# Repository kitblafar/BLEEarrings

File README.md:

# Bluetooth Low-Energy Earrings

A set of bluetooth BLE earrings inspired by the movie blade runner.

Including custom pendant, earring and earring charging dock PCBs; custom 3D printed enclosure; embedded solution on NRF52833 and bluetooth app.

This earring blink different colours dependant on messages sent over Bluetooth by the bluetooth app. The solution includes a pendant that holds the LED and is connected by wiring that passes through the ear piercing; the earring itself that sits behind the ear and a charging and programming dock including USB hub. The earrings are flashed and charged over USB C connectors and are powered by drone batteries so include custom charge protection and power path management circuits.

Project phase: PCB ordered and received, BOM finalised and ordered, first revision of enclosure made, first iteration of the embedded solution.

Next step: test PCBs and NRF52833 code, order batteries, print enclosure, start developing the app.

This is a collab with [Dominic Mason](https://github.com/dominicmason555/)

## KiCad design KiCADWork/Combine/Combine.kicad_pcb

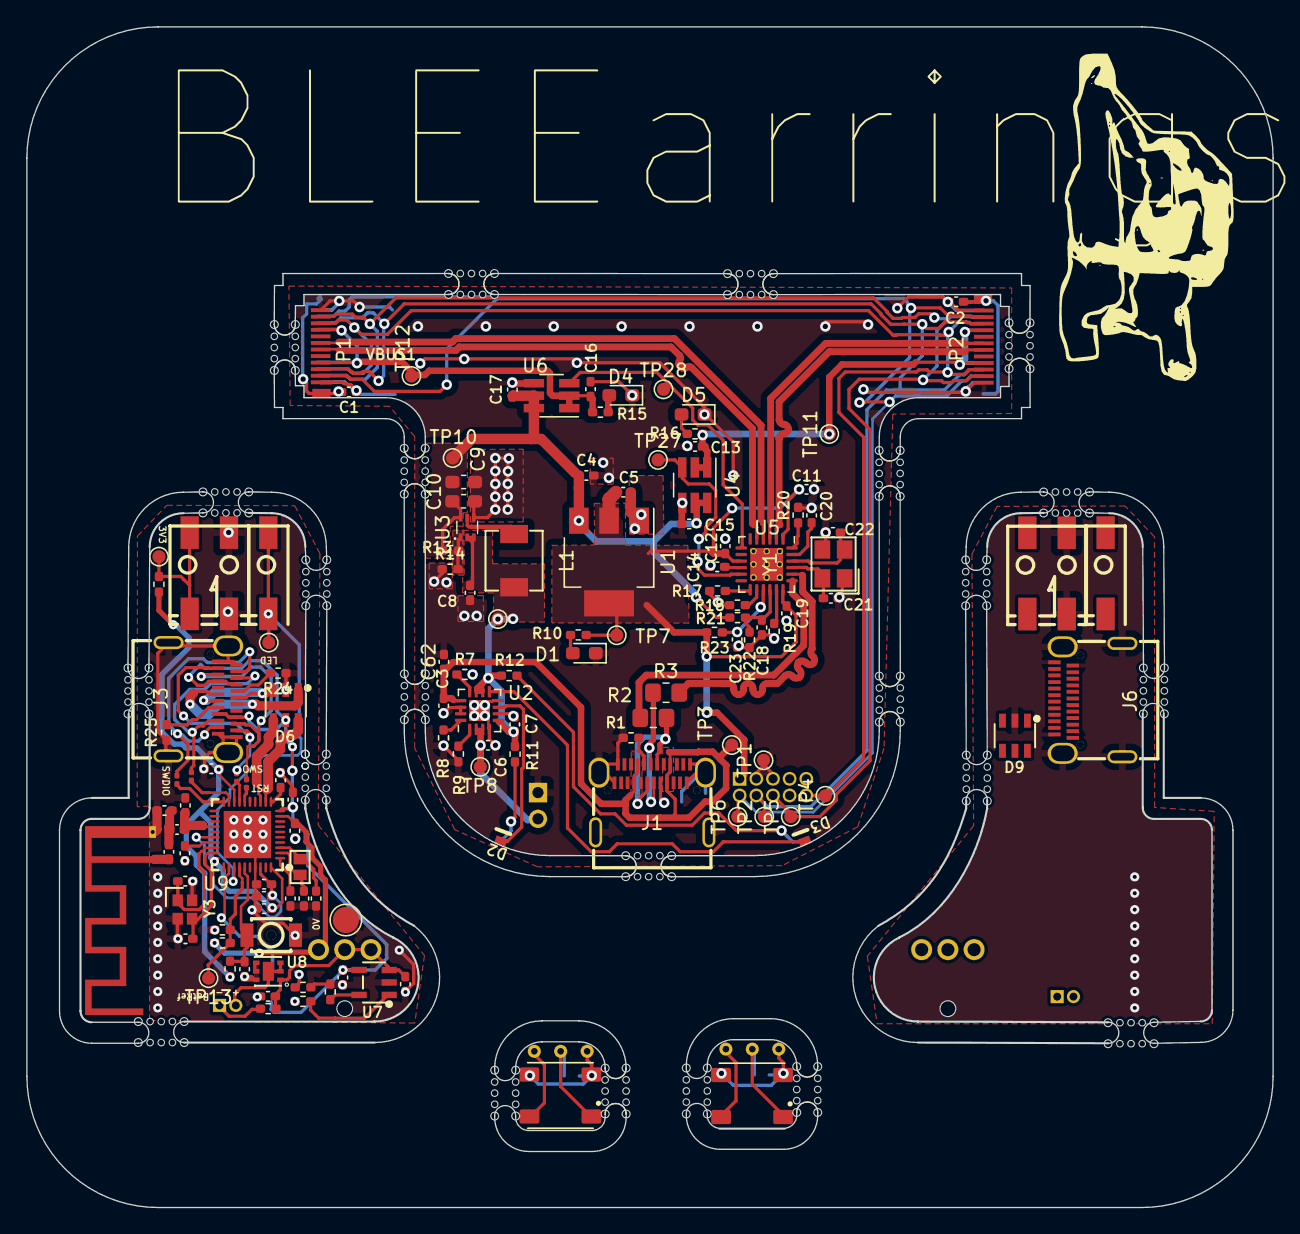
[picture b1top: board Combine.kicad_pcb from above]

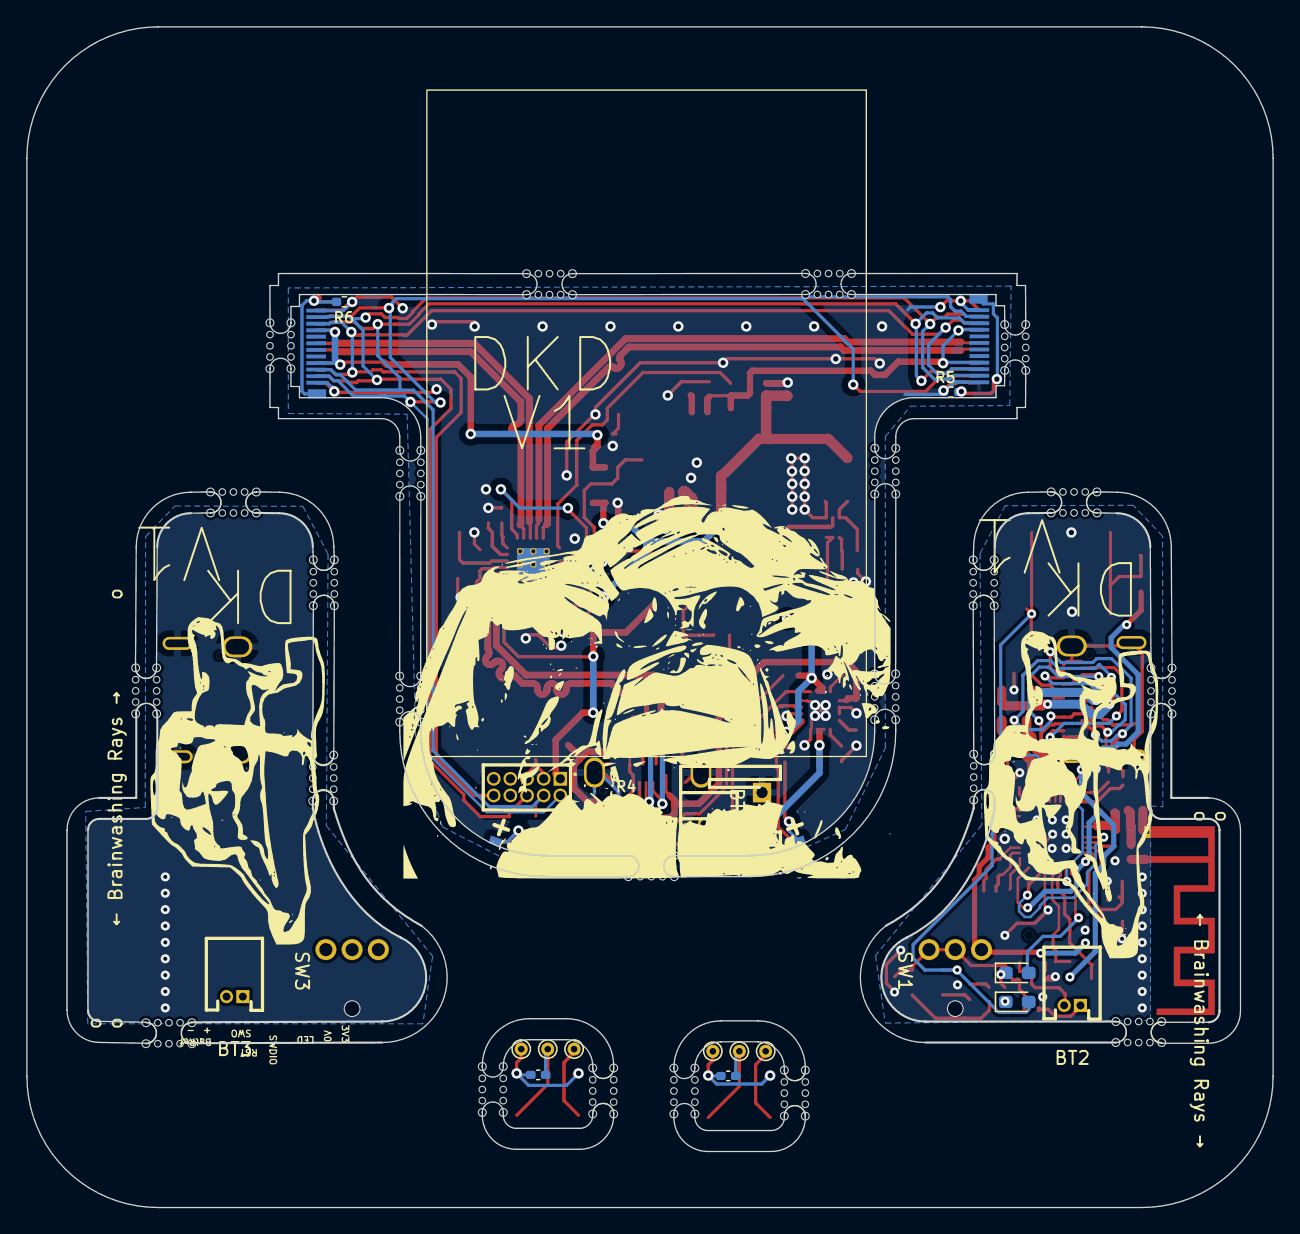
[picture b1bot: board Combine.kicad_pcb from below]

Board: 2 copper layers, 95.0 x 90.0 mm, 149 parts (19 on the bottom side), 98 nets.

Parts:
ANT1: Texas_SWRA117D_2.4GHz_Left
BT1: Battery; CONN-TH_S2B-PH-K-S-LF-SN
BT2, BT3: Battery; CONN-TH_530480210
C1, C2, C11, C13, C16, C18, C19, C20, C25, C30, C33, C41, C63, C64: 100n; C_0402_1005Metric_Pad0.74x0.62mm_HandSolder
C3, C12, C14, C23, C34, C38: 1u; C_0402_1005Metric_Pad0.74x0.62mm_HandSolder
C4, C5: 2.2u; C_0402_1005Metric_Pad0.74x0.62mm_HandSolder
C6, C7, C15, C17, C28, C29, C31: 4.7u; C_0402_1005Metric_Pad0.74x0.62mm_HandSolder
C8, C24, C26, C62: 10u; C_0402_1005Metric_Pad0.74x0.62mm_HandSolder
C9, C10: 22u; C_0603_1608Metric_Pad1.08x0.95mm_HandSolder
C21, C22: 18p; C_0402_1005Metric_Pad0.74x0.62mm_HandSolder
C27, C32: 8p; C_0402_1005Metric_Pad0.74x0.62mm_HandSolder
C35: 1p; C_0402_1005Metric_Pad0.74x0.62mm_HandSolder
C36: 100p; C_0402_1005Metric_Pad0.74x0.62mm_HandSolder
C37: 1.2p; C_0402_1005Metric_Pad0.74x0.62mm_HandSolder
C39: NC; C_0402_1005Metric_Pad0.74x0.62mm_HandSolder
C40, C42: 12p; C_0402_1005Metric_Pad0.74x0.62mm_HandSolder
D1: LED; LED_0603_1608Metric_Pad1.05x0.95mm_HandSolder
D2: BLUE RED; SideStuckLED
D3: BLUE LED; SideStuckLED
D4, D5, D8: BLUE LED; LED_0603_1608Metric_Pad1.05x0.95mm_HandSolder
D6, D9: USBLC6-2SC6_C2687116; SOT-23-6_L2.9-W1.6-P0.95-LS2.8-BL
D7: RED LED; LED_0603_1608Metric_Pad1.05x0.95mm_HandSolder
D12, D13: 2758; SOL320P540X170-4N
J1, J3, J6: USB_C_Receptacle; TYPE-C-SMD_C9900025773
J2: Conn_01x10_Socket; HDR-TH_10P-P1.27-V-M-R2-C5-S1.27-1
J4, J7: Screw_Terminal_01x01; CONN-SMD_custom1
J5, J8: Screw_Terminal_01x02; CONN-SMD_2059-302
L1: 4.7u; IND-SMD_L4.4-W4.2
L2: 4.7n; L_0402_1005Metric_Pad0.77x0.64mm_HandSolder
L3: 2.2n; L_0402_1005Metric_Pad0.77x0.64mm_HandSolder
P1, P2: USB_C_Plug; USB-C-SMD_TYPE-C-24P-GTJB-040
R1, R4, R24, R25: 5k1; R_0402_1005Metric_Pad0.72x0.64mm_HandSolder
R2, R3: 0R; R_0805_2012Metric_Pad1.20x1.40mm_HandSolder
R5, R6: 1k; R_0402_1005Metric_Pad0.72x0.64mm_HandSolder
R7, R11, R12: 1.18k; R_0402_1005Metric_Pad0.72x0.64mm_HandSolder
R8: 1.78k; R_0402_1005Metric_Pad0.72x0.64mm_HandSolder
R9, R21, R22, R23: 10k; R_0402_1005Metric_Pad0.72x0.64mm_HandSolder
R10, R26, R37: 2k; R_0402_1005Metric_Pad0.72x0.64mm_HandSolder
R13: 732; R_0402_1005Metric_Pad0.72x0.64mm_HandSolder
R14, R34: 100k; R_0402_1005Metric_Pad0.72x0.64mm_HandSolder
R15, R16, R29: 220; R_0402_1005Metric_Pad0.72x0.64mm_HandSolder
R17, R18, R19, R28: 100; R_0402_1005Metric_Pad0.72x0.64mm_HandSolder
R20: 12k; R_0402_1005Metric_Pad0.72x0.64mm_HandSolder
R27: 4k99; R_0402_1005Metric_Pad0.72x0.64mm_HandSolder
R30, R31, R32, R33: NF; R_0201_0603Metric
R35: 33k; R_0402_1005Metric_Pad0.72x0.64mm_HandSolder
R36: 470; R_0402_1005Metric_Pad0.72x0.64mm_HandSolder
SW1, SW3: TK-6580B-1; SW-TH_TK-6580B-1
SW2: SW_DIP_x01; KEY-SMD_L3.0-W2.5-LS4.0
TP1, TP2, TP3, TP4, TP5, TP6, TP7, TP8, TP9, TP10, TP11, TP12, TP13, TP14, TP15, TP27, TP28: TestPoint; TestPoint_Pad_D1.0mm
TP16: TestPoint; TestPoint_Pad_D2.0mm
TP21, TP22, TP23, TP24, TP25, TP26: TestPoint; TestPoint_THTPad_D1.0mm_Drill0.5mm
U1: AMS1117-3.3; SOT-223-3_TabPin2
U2: BQ24073RGT; VQFN-16-1EP_3x3mm_P0.5mm_EP1.6x1.6mm
U3: TPS61023DRLR; SOT-563_L1.6-W1.2-P0.50-LS1.6-BR
U4, U6: SIP32509DT-T1-GE3; SOT-23-6_Handsoldering
U5: USB2422T-I/MJ; HVQFN-24-1EP_4x4mm_P0.5mm_EP2.5x2.5mm_ThermalVias
U7: MCP73831T-2ACI/OT; SOT-23-5_L3.0-W1.7-P0.95-LS2.8-BL
U8: XB6096I2SV; WDFN-6_L2.0-W2.0-P0.65-BL-EP
U9: NRF52833-QDAA-R7; QFN-40_L5.0-W5.0-P0.40-TL-EP3.6
Y1: X322524MOB4SI; CRYSTAL-SMD_4P-L3.2-W2.5-BL
Y2: X161032768KLD2SI; CRYSTAL-SMD_L1.6-W1.0
Y3: XL7EL89CKI-111YLC-32M; CRYSTAL-SMD_4P-L2.0-W1.6-BL

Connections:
+3V3: C5.1, C11.2, C12.2, C19.2, C30.1, C34.2, J2.1, R10.2, R23.2, R36.2, R37.2, TP7.1, U1.2 (VO), U5.1 (VDD33), U5.9 (VDD33), U5.18 (VDD33), U9.18 (VDD), U9.30 (VDD), U9.40 (VDD)
+BATT: C28.2, R34.2, SW1.3, SW3.3, U9.9 (VDDH)
/Dock/DeviceSelect/D1+: P2.A6 (D+), U5.3 (USBDP_DN1/PRT_DIS_P1)
/Dock/DeviceSelect/D1-: P2.A7 (D-), U5.2 (USBDM_DN1/PRT_DIS_M1)
/Dock/DeviceSelect/D2+: P1.A6 (D+), U5.5 (USBDP_DN2/PRT_DIS_P2)
/Dock/DeviceSelect/D2-: P1.A7 (D-), U5.4 (USBDM_DN2/PRT_DIS_M2)
/Dock/DeviceSelect/D+: R3.1, U5.20 (USBDP_UP)
/Dock/DeviceSelect/D-: R2.2, U5.19 (USBDM_UP)
/Dock/DeviceSelect/VBUS1: C13.2, P2.A4 (VBUS), P2.A9 (VBUS), P2.B4 (VBUS), P2.B9 (VBUS), R16.1, TP11.1, U4.1 (OUT), U4.2 (OUT)
/Dock/DeviceSelect/VBUS2: C16.2, P1.A4 (VBUS), P1.A9 (VBUS), P1.B4 (VBUS), P1.B9 (VBUS), R15.1, TP12.1, U6.1 (OUT), U6.2 (OUT)
/Dock/DeviceSelect/Vsys: C4.1, C9.1, C10.1, C15.2, C17.2, R13.2, R21.2, TP10.1, U1.3 (VI), U3.6 (VOUT), U4.5 (IN), U4.6 (IN), U6.5 (IN), U6.6 (IN)
/Dock/ExtraBattery/3.7Out: C7.1, C8.1, L1.1, R11.2, R12.2, TP9.1, U2.5 (EN2), U2.10 (OUT), U2.11 (OUT), U3.2 (EN), U3.3 (VIN)
/Dock/ExtraBattery/FB: R13.1, R14.2, U3.1 (FB)
/Dock/ExtraBattery/VBAT: BT1.1 (+), C6.1, TP8.1, U2.2 (BAT), U2.3 (BAT)
/Dock/ExtraBattery/VBUS: C3.1, C62.1, J1.A4 (VBUS), TP3.1, U2.13 (IN)
/Earring1/DSP/VBUS: C26.1, C29.2, D6.5 (VBUS), D7.2 (A), J3.A4 (VBUS), U7.4 (VDD), U9.10 (VBUS)
/Earring1/DSP/nReset: J3.A10 (RX2-), J3.B10 (RX1-), R32.1
/Earring1/Power/VBAT: C24.1, C25.1, R28.2, SW1.1, SW1.2, U7.3 (VBAT), U8.1 (VDD)
/Earring2/DSP/VBUS: D9.5 (VBUS), J6.A4 (VBUS)
/Earring2/DSP/nReset: J6.A10 (RX2-), J6.B10 (RX1-)
/Earring2/Power/VBAT: SW3.1, SW3.2
BatRef: R34.1, R35.2, TP13.1, U9.34 (P0.29_AIN5)
D+: D6.4 (I/O2), D9.4 (I/O2), U9.13 (D+)
D-: D6.6 (I/O1), D9.6 (I/O1), U9.12 (D-)
DEC6: C38.1, C39.1, U9.26 (DEC6), U9.38 (DEC4)
GND: ANT1.2 (GND), BT1.2 (-), C1.1, C2.1, C3.2, C4.2, C5.2, C6.2, C7.2, C8.2, C9.2, C10.2, C11.1, C12.1, C13.1, C14.1, C15.1, C16.1, C17.1, C18.1, C19.1, C20.1, C21.2, C22.1, C23.1, C24.2, C25.2, C26.2, C27.1, C28.1, C29.1, C30.2, C31.1, C32.1, C33.1, C34.1, C35.2, C36.2, C37.2, C38.2, C39.2, C40.1, C41.1, C42.1, C62.2, D1.1 (K), D4.1 (K), D5.1 (K), D6.2 (GND), D9.2 (GND), J1.A1 (GND), J1.S1 (SHIELD), J2.3, J2.5, J3.A1 (GND), J3.S1 (SHIELD), J5.2, J6.A1 (GND), J6.S1 (SHIELD), J8.2, P1.A1 (GND), P2.A1 (GND), R1.1, R4.1, R5.2, R6.2, R7.2, R8.2, R9.1, R14.1, R17.1, R18.1, R19.1, R20.1, R22.1, R24.1, R25.1, R27.2, R29.1, R35.1, SW2.2, TP1.1, TP16.1, U1.1 (GND), U2.4 (~CE), U2.6 (EN1), U2.8 (VSS), U2.14 (TMR), U2.15 (TD), U2.17 (VSS), U3.4 (GND), U4.4 (GND), U5.25 (EP), U6.4 (GND), U7.2 (VSS), U8.4 (VM), U8.5 (VM), U8.6 (VM), U9.37 (VSS), U9.41 (VSS), Y1.1, Y1.3, Y3.2, Y3.3
LED_A: D8.2 (A), U9.32 (P0.02_AIN0)
NEO_LED: J4.1, J7.1, TP14.1, U9.33 (P0.28_AIN4)
unnamed: ANT1.1 (FP), L3.2
unnamed: BT2.1 (+), R28.1
unnamed: BT2.2 (-), U8.2 (GND), U8.3 (GND), U8.7 (EP)
unnamed: C37.1, L2.2, L3.1
unnamed: D1.2 (A), R10.1
unnamed: D2.2 (A), R11.1
unnamed: D2.1 (K), U2.7 (~PGOOD)
unnamed: D3.2 (A), R12.1
unnamed: D3.1 (K), U2.9 (~CHG)
unnamed: D4.2 (A), R15.2
unnamed: D5.2 (A), R16.2
unnamed: D6.1 (I/O1), J3.A7 (D-), J3.B7 (D-)
unnamed: D6.3 (I/O2), J3.A6 (D+), J3.B6 (D+)
unnamed: D7.1 (K), R26.1
unnamed: D8.1 (K), R29.2
unnamed: D9.1 (I/O1), J6.A7 (D-), J6.B7 (D-)
unnamed: D9.3 (I/O2), J6.A6 (D+), J6.B6 (D+)
unnamed: D12.4 (DIN), TP21.1
unnamed: C63.1, D12.2 (DOUT), D12.3 (VSS), TP23.1
unnamed: C63.2, D12.1 (VDD), TP22.1
unnamed: D13.4 (DIN), TP24.1
unnamed: C64.1, D13.2 (DOUT), D13.3 (VSS), TP26.1
unnamed: C64.2, D13.1 (VDD), TP25.1
unnamed: J1.A5 (CC1), R1.2
unnamed: J1.B5 (CC2), R4.2
unnamed: J1.A6 (D+), J1.B6 (D+), R3.2
unnamed: J1.A7 (D-), J1.B7 (D-), R2.1
unnamed: J3.A5 (CC1), R24.2
unnamed: J3.B5 (CC2), R25.2
unnamed: J5.1, R36.1, TP15.1
unnamed: C1.2, P1.S1 (SHIELD), R5.1
unnamed: C2.2, P2.S1 (SHIELD), R6.1
unnamed: R7.1, U2.12 (ILIM)
unnamed: R8.1, U2.16 (ISET)
unnamed: R9.2, U2.1 (TS)
unnamed: L1.2, U3.5 (SW)
unnamed: C14.2, U5.10 (CRFILT)
unnamed: C20.2, U5.23 (PLLFILT)
unnamed: R20.2, U5.24 (RBIAS)
unnamed: R18.2, U5.14 (SMBCLK/CFG_SEL0)
unnamed: R17.2, U5.13 (SMBDATA/NON_REM1)
unnamed: R19.2, U5.17 (SUSP_IND/LOCAL_PWR/(NON_REM0))
unnamed: C18.2, R21.1, R22.2, U5.16 (VBUS_DET)
unnamed: C22.2, U5.22 (XTALIN/CLKIN), Y1.2
unnamed: C21.1, U5.21 (XTALOUT/(CLKIN_EN)), Y1.4
unnamed: R27.1, U7.5 (PROG)
unnamed: R26.2, U7.1 (STAT)
unnamed: C35.1, L2.1, U9.24 (ANT)
unnamed: C33.2, U9.1 (DEC1)
unnamed: C36.1, U9.27 (DEC3)
unnamed: C31.2, U9.11 (DECUSB)
unnamed: C27.2, U9.2 (P0.00_XL1), Y2.2
unnamed: C32.2, U9.3 (P0.01_XL2), Y2.1
unnamed: R32.2, U9.16 (P0.18_nRESET)
unnamed: R30.1, U9.17 (P0.20)
unnamed: R31.1, U9.20 (SWDCLK)
unnamed: R33.2, U9.19 (SWDIO)
unnamed: C42.2, U9.28 (XC1), Y3.1
unnamed: C40.2, U9.29 (XC2), Y3.4
PWREN1: TP27.1, U4.3 (EN), U5.11 (PRTPWR2)
PWREN2: TP28.1, U5.7 (PRTPWR1/(BC_EN1)), U6.3 (EN)
Pair: C41.2, R37.1, SW2.1, U9.35 (P0.30_AIN6)
RESET: C23.2, R23.1, U5.15 (RESET_N)
SWCLK: J2.4, P1.A3 (TX1-), P1.B3 (TX2-), P2.A3 (TX1-), P2.B3 (TX2-), TP2.1
SWDCLK_L: J3.A3 (TX1-), J3.B3 (TX2-), J6.A3 (TX1-), J6.B3 (TX2-), R33.1
SWDIO: J2.2, P1.A2 (TX1+), P1.B2 (TX2+), P2.A2 (TX1+), P2.B2 (TX2+), TP6.1
SWDIO_L: J3.A2 (TX1+), J3.B2 (TX2+), J6.A2 (TX1+), J6.B2 (TX2+), R31.2
SWO: J2.6, P1.A11 (RX2+), P1.B11 (RX1+), P2.A11 (RX2+), P2.B11 (RX1+), TP5.1
SWO_L: J3.A11 (RX2+), J3.B11 (RX1+), J6.A11 (RX2+), J6.B11 (RX1+), R30.2
nRESET: J2.10, P1.A10 (RX2-), P1.B10 (RX1-), P2.A10 (RX2-), P2.B10 (RX1-), TP4.1

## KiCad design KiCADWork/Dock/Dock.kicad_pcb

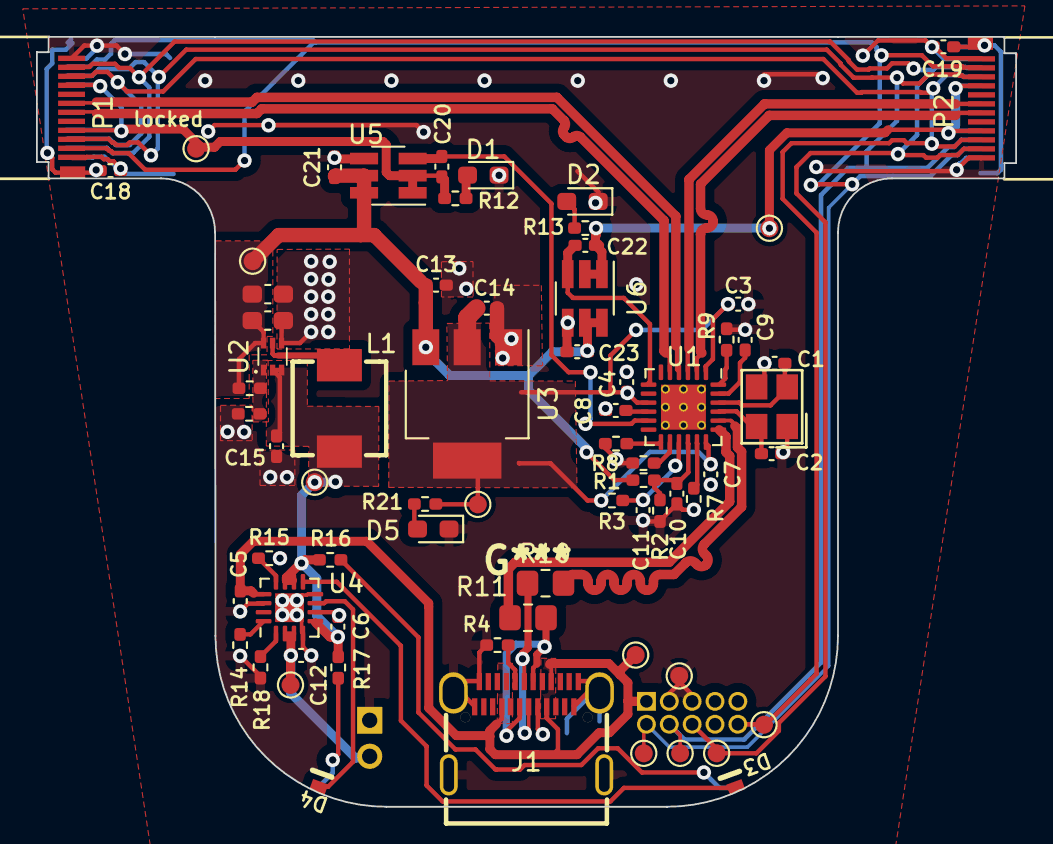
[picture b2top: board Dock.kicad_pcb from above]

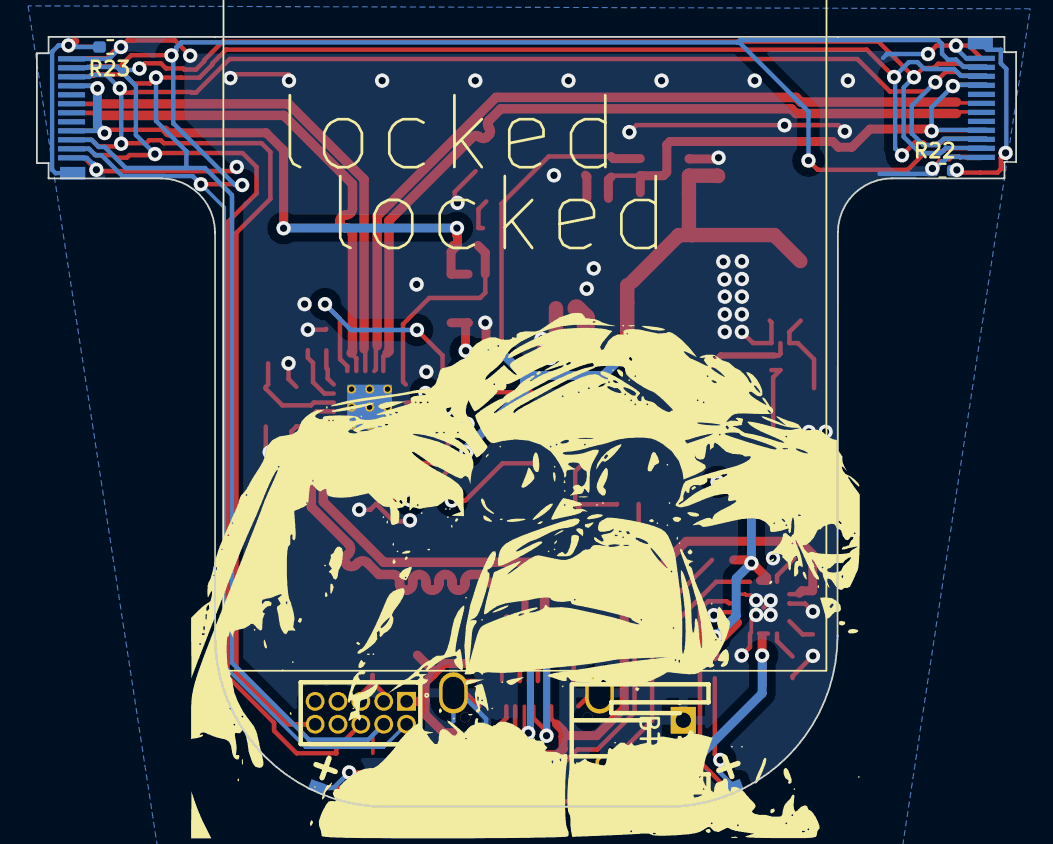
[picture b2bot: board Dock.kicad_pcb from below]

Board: 2 copper layers, 54.4 x 42.8 mm, 76 parts (5 on the bottom side), 48 nets.

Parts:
BT2: Battery; CONN-TH_S2B-PH-K-S-LF-SN
C1, C2: 18p; C_0402_1005Metric_Pad0.74x0.62mm_HandSolder
C3, C7, C9, C10, C18, C19, C20, C22: 100n; C_0402_1005Metric_Pad0.74x0.62mm_HandSolder
C4, C5, C8, C11: 1u; C_0402_1005Metric_Pad0.74x0.62mm_HandSolder
C6, C12, C21, C23: 4.7u; C_0402_1005Metric_Pad0.74x0.62mm_HandSolder
C13, C14: 2.2u; C_0402_1005Metric_Pad0.74x0.62mm_HandSolder
C15: 10u; C_0402_1005Metric_Pad0.74x0.62mm_HandSolder
C16, C17: 22u; C_0603_1608Metric_Pad1.08x0.95mm_HandSolder
D1, D2: BLUE LED; LED_0603_1608Metric_Pad1.05x0.95mm_HandSolder
D3: BLUE LED; SideStuckLED
D4: BLUE RED; SideStuckLED
D5: LED; LED_0603_1608Metric_Pad1.05x0.95mm_HandSolder
J1: USB_C_Receptacle; TYPE-C-SMD_C9900025773
J4: Conn_01x10_Socket; HDR-TH_10P-P1.27-V-M-R2-C5-S1.27-1
L1: 4.7u; IND-SMD_L5.2-W5.2_YSPI0530
P1, P2: USB_C_Plug; USB-C-SMD_TYPE-C-24P-GTJB-040
R1, R2, R3, R18: 10k; R_0402_1005Metric_Pad0.72x0.64mm_HandSolder
R4, R5: 5k1; R_0402_1005Metric_Pad0.72x0.64mm_HandSolder
R6, R7, R8: 100; R_0402_1005Metric_Pad0.72x0.64mm_HandSolder
R9: 12k; R_0402_1005Metric_Pad0.72x0.64mm_HandSolder
R10, R11: 0R; R_0805_2012Metric_Pad1.20x1.40mm_HandSolder
R12, R13: 220; R_0402_1005Metric_Pad0.72x0.64mm_HandSolder
R14: 1.78k; R_0402_1005Metric_Pad0.72x0.64mm_HandSolder
R15, R16, R17: 1.18k; R_0402_1005Metric_Pad0.72x0.64mm_HandSolder
R19: 100k; R_0402_1005Metric_Pad0.72x0.64mm_HandSolder
R20: 732; R_0402_1005Metric_Pad0.72x0.64mm_HandSolder
R21: 2k; R_0402_1005Metric_Pad0.72x0.64mm_HandSolder
R22, R23: 1k; R_0402_1005Metric_Pad0.72x0.64mm_HandSolder
TP3, TP4, TP6, TP7, TP8, TP10, TP11, TP12, TP13, TP14, TP16, TP17: TestPoint; TestPoint_Pad_D1.0mm
U1: USB2422T-I/MJ; HVQFN-24-1EP_4x4mm_P0.5mm_EP2.5x2.5mm_ThermalVias
U2: TPS61023DRLR; SOT-563_L1.6-W1.2-P0.50-LS1.6-BR
U3: AMS1117-3.3; SOT-223-3_TabPin2
U4: BQ24073RGT; VQFN-16-1EP_3x3mm_P0.5mm_EP1.6x1.6mm
U5, U6: SIP32509DT-T1-GE3; SOT-23-6_Handsoldering
Y1: X322524MOB4SI; CRYSTAL-SMD_4P-L3.2-W2.5-BL

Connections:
+3V3: C3.2, C4.2, C7.2, C14.1, R3.2, R21.2, TP10.1, U1.1 (VDD33), U1.9 (VDD33), U1.18 (VDD33), U3.2 (VO)
/DeviceSelect/D1+: P1.A6 (D+), U1.5 (USBDP_DN2/PRT_DIS_P2)
/DeviceSelect/D1-: P1.A7 (D-), U1.4 (USBDM_DN2/PRT_DIS_M2)
/DeviceSelect/D2+: P2.A6 (D+), U1.3 (USBDP_DN1/PRT_DIS_P1)
/DeviceSelect/D2-: P2.A7 (D-), U1.2 (USBDM_DN1/PRT_DIS_M1)
/DeviceSelect/D+: R10.1, U1.20 (USBDP_UP)
/DeviceSelect/D-: R11.2, U1.19 (USBDM_UP)
/DeviceSelect/VBUS1: C20.2, P1.A4 (VBUS), P1.A9 (VBUS), P1.B4 (VBUS), P1.B9 (VBUS), R12.1, TP3.1, U5.1 (OUT), U5.2 (OUT)
/DeviceSelect/VBUS2: C22.2, P2.A4 (VBUS), P2.A9 (VBUS), P2.B4 (VBUS), P2.B9 (VBUS), R13.1, TP4.1, U6.1 (OUT), U6.2 (OUT)
/DeviceSelect/Vsys: C13.1, C16.1, C17.1, C21.2, C23.2, R1.2, R20.2, TP6.1, U2.6 (VOUT), U3.3 (VI), U5.5 (IN), U5.6 (IN), U6.5 (IN), U6.6 (IN)
/ExtraBattery/3.7Out: C6.1, C15.1, L1.1, R16.2, R17.2, TP7.1, U2.2 (EN), U2.3 (VIN), U4.5 (EN2), U4.10 (OUT), U4.11 (OUT)
/ExtraBattery/FB: R19.2, R20.1, U2.1 (FB)
/ExtraBattery/VBAT: BT2.1 (+), C12.1, TP8.1, U4.2 (BAT), U4.3 (BAT)
GND: BT2.2 (-), C1.1, C2.2, C3.1, C4.1, C5.2, C6.2, C7.1, C8.1, C9.1, C10.1, C11.1, C12.2, C13.2, C14.2, C15.2, C16.2, C17.2, C18.1, C19.1, C21.1, C23.1, D1.1 (K), D2.1 (K), D5.1 (K), J1.A1 (GND), J1.S1 (SHIELD), J4.3, J4.5, P1.A1 (GND), P2.A1 (GND), R2.1, R4.1, R5.1, R6.1, R7.1, R8.1, R9.1, R14.2, R15.2, R18.1, R19.1, R22.2, R23.2, TP17.1, U1.25 (EP), U2.4 (GND), U3.1 (GND), U4.4 (~CE), U4.6 (EN1), U4.8 (VSS), U4.14 (TMR), U4.17 (VSS), U5.4 (GND), U6.4 (GND), Y1.1, Y1.3
unnamed: D1.2 (A), R12.2
unnamed: D2.2 (A), R13.2
unnamed: D3.2 (A), R16.1
unnamed: D3.1 (K), U4.9 (~CHG)
unnamed: D4.2 (A), R17.1
unnamed: D4.1 (K), U4.7 (~PGOOD)
unnamed: D5.2 (A), R21.1
unnamed: J1.A5 (CC1), R4.2
unnamed: J1.B5 (CC2), R5.2
unnamed: J1.A6 (D+), J1.B6 (D+), R10.2
unnamed: J1.A7 (D-), J1.B7 (D-), R11.1
unnamed: C18.2, P1.S1 (SHIELD), R22.1
unnamed: C19.2, P2.S1 (SHIELD), R23.1
unnamed: C8.2, U1.10 (CRFILT)
unnamed: C9.2, U1.23 (PLLFILT)
unnamed: R9.2, U1.24 (RBIAS)
unnamed: R8.2, U1.14 (SMBCLK/CFG_SEL0)
unnamed: R6.2, U1.13 (SMBDATA/NON_REM1)
unnamed: R7.2, U1.17 (SUSP_IND/LOCAL_PWR/(NON_REM0))
unnamed: C10.2, R1.1, R2.2, U1.16 (VBUS_DET)
unnamed: C1.2, U1.22 (XTALIN/CLKIN), Y1.2
unnamed: C2.1, U1.21 (XTALOUT/(CLKIN_EN)), Y1.4
unnamed: L1.2, U2.5 (SW)
unnamed: R15.1, U4.12 (ILIM)
unnamed: R14.1, U4.16 (ISET)
unnamed: R18.2, U4.1 (TS)
PWREN1: C20.1, U1.11 (PRTPWR2), U5.3 (EN)
PWREN2: C22.1, U1.7 (PRTPWR1/(BC_EN1)), U6.3 (EN)
RESET: C11.2, R3.1, U1.15 (RESET_N)
SWCLK: J4.4, P1.A3 (TX1-), P1.B3 (TX2-), P2.A3 (TX1-), P2.B3 (TX2-), TP13.1
SWDIO: J4.2, P1.A2 (TX1+), P1.B2 (TX2+), P2.A2 (TX1+), P2.B2 (TX2+), TP12.1
SWO: J4.6, P1.A11 (RX2+), P1.B11 (RX1+), P2.A11 (RX2+), P2.B11 (RX1+), TP14.1
VTRef: C5.1, J1.A4 (VBUS), J4.1, TP11.1, U4.13 (IN)
nRESET: J4.10, P1.A10 (RX2-), P1.B10 (RX1-), P2.A10 (RX2-), P2.B10 (RX1-), TP16.1

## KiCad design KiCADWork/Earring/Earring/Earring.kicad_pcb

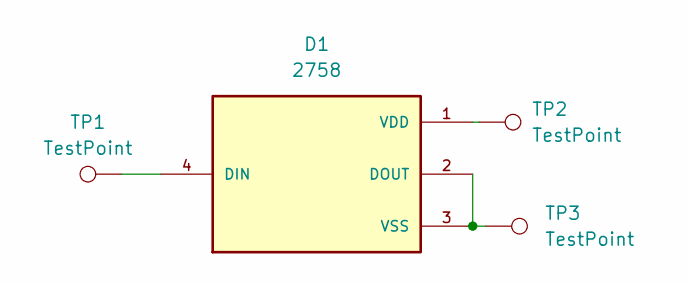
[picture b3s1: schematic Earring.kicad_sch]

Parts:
D1: 2758; SOL320P540X170-4N; PARTREV 01
TP1, TP2, TP3: TestPoint; TestPoint_THTPad_D1.0mm_Drill0.5mm

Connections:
unnamed: D1.4 (DIN), TP1.1
unnamed: D1.2 (DOUT), D1.3 (VSS), TP3.1
unnamed: D1.1 (VDD), TP2.1

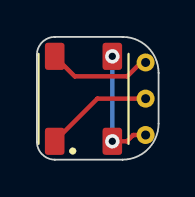
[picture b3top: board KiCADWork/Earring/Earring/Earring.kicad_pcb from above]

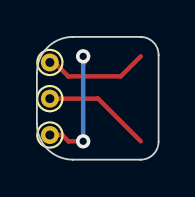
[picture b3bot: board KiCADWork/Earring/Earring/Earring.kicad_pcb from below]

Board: 2 copper layers, 6.8 x 6.8 mm, 4 parts (3 on the bottom side), 3 nets.

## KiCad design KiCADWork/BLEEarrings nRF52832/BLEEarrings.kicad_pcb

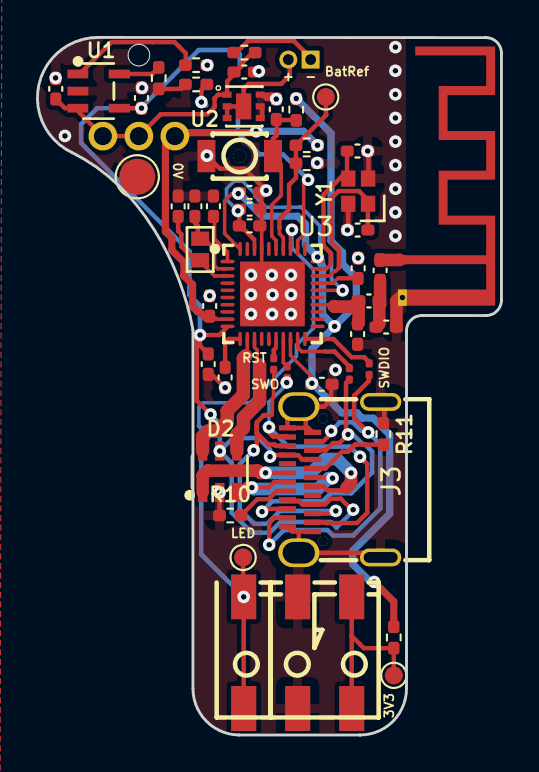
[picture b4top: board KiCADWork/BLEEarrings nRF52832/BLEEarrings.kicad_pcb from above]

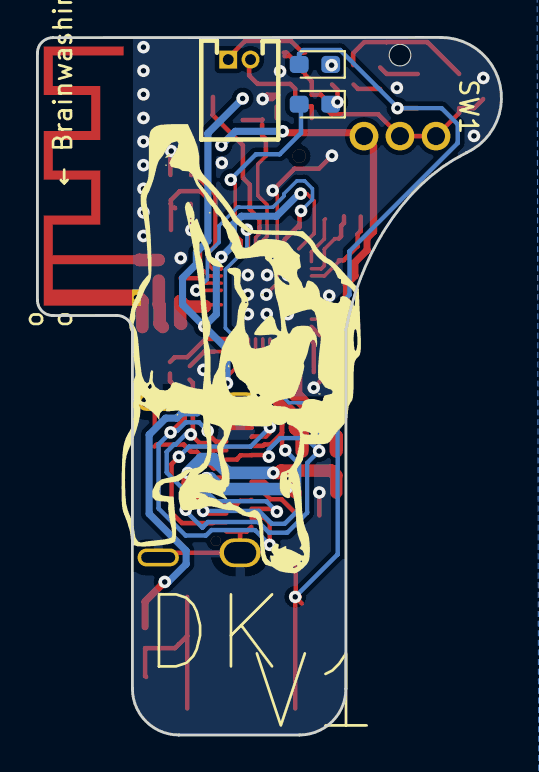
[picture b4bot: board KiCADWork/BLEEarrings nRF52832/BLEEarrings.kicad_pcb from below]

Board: 2 copper layers, 25.8 x 38.8 mm, 54 parts (4 on the bottom side), 41 nets.

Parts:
ANT1: Texas_SWRA117D_2.4GHz_Left
BT1: Battery; CONN-TH_530480210
C1, C7: 1u; C_0402_1005Metric_Pad0.74x0.62mm_HandSolder
C2, C6, C14, C18: 100n; C_0402_1005Metric_Pad0.74x0.62mm_HandSolder
C3, C4: 12p; C_0402_1005Metric_Pad0.74x0.62mm_HandSolder
C5: 1.2p; C_0402_1005Metric_Pad0.74x0.62mm_HandSolder
C8: 1p; C_0402_1005Metric_Pad0.74x0.62mm_HandSolder
C9, C10, C12: 4.7u; C_0402_1005Metric_Pad0.74x0.62mm_HandSolder
C11: 100p; C_0402_1005Metric_Pad0.74x0.62mm_HandSolder
C13, C19: 10u; C_0402_1005Metric_Pad0.74x0.62mm_HandSolder
C15, C16: 8p; C_0402_1005Metric_Pad0.74x0.62mm_HandSolder
C17: NC; C_0402_1005Metric_Pad0.74x0.62mm_HandSolder
D1: RED LED; LED_0603_1608Metric_Pad1.05x0.95mm_HandSolder
D2: USBLC6-2SC6_C2687116; SOT-23-6_L2.9-W1.6-P0.95-LS2.8-BL
D4: BLUE LED; LED_0603_1608Metric_Pad1.05x0.95mm_HandSolder
J1: Screw_Terminal_01x01; CONN-SMD_custom1
J2: Screw_Terminal_01x02; CONN-SMD_2059-302
J3: USB_C_Receptacle; TYPE-C-SMD_C9900025773
L1: 4.7n; L_0402_1005Metric_Pad0.77x0.64mm_HandSolder
L2: 2.2n; L_0402_1005Metric_Pad0.77x0.64mm_HandSolder
R1, R2: 2k; R_0402_1005Metric_Pad0.72x0.64mm_HandSolder
R3: 100; R_0402_1005Metric_Pad0.72x0.64mm_HandSolder
R4: 4k99; R_0402_1005Metric_Pad0.72x0.64mm_HandSolder
R5, R6, R7, R8: NF; R_0201_0603Metric
R9: 470; R_0402_1005Metric_Pad0.72x0.64mm_HandSolder
R10, R11: 5k1; R_0402_1005Metric_Pad0.72x0.64mm_HandSolder
R12: 220; R_0402_1005Metric_Pad0.72x0.64mm_HandSolder
R13: 100k; R_0402_1005Metric_Pad0.72x0.64mm_HandSolder
R14: 33k; R_0402_1005Metric_Pad0.72x0.64mm_HandSolder
SW1: TK-6580B-1; SW-TH_TK-6580B-1
SW2: SW_DIP_x01; KEY-SMD_L3.0-W2.5-LS4.0
TP9, TP10, TP11: TestPoint; TestPoint_Pad_D1.0mm
TP16: TestPoint; TestPoint_Pad_D2.0mm
U1: MCP73831T-2ACI/OT; SOT-23-5_L3.0-W1.7-P0.95-LS2.8-BL
U2: XB6096I2SV; WDFN-6_L2.0-W2.0-P0.65-BL-EP
U3: NRF52833-QDAA-R7; QFN-40_L5.0-W5.0-P0.40-TL-EP3.6
Y1: XL7EL89CKI-111YLC-32M; CRYSTAL-SMD_4P-L2.0-W1.6-BL
Y2: X161032768KLD2SI; CRYSTAL-SMD_L1.6-W1.0

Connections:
+3V3: C1.2, C6.1, R2.2, R9.2, U3.18 (VDD), U3.30 (VDD), U3.40 (VDD)
+BATT: C12.2, R13.2, SW1.3, U3.9 (VDDH)
/DSP/VBUS: C10.2, C19.1, D1.2 (A), D2.5 (VBUS), J3.A4 (VBUS), U1.4 (VDD), U3.10 (VBUS)
/DSP/nReset: J3.A10 (RX2-), J3.B10 (RX1-), R5.1
/Power/VBAT: C13.1, C18.1, R3.2, SW1.1, SW1.2, U1.3 (VBAT), U2.1 (VDD)
BatRef: R13.1, R14.2, TP9.1, U3.34 (P0.29_AIN5)
D+: D2.4 (I/O2), U3.13 (D+)
D-: D2.6 (I/O1), U3.12 (D-)
DEC6: C7.1, C17.1, U3.26 (DEC6), U3.38 (DEC4)
GND: ANT1.2 (GND), C1.1, C2.1, C3.1, C4.1, C5.2, C6.2, C7.2, C8.2, C9.1, C10.1, C11.2, C12.1, C13.2, C14.1, C15.1, C16.1, C17.2, C18.2, C19.2, D2.2 (GND), J2.2, J3.A1 (GND), J3.S1 (SHIELD), R4.2, R10.1, R11.1, R12.1, R14.1, SW2.2, TP16.1, U1.2 (VSS), U2.4 (VM), U2.5 (VM), U2.6 (VM), U3.37 (VSS), U3.41 (VSS), Y1.2, Y1.3
LED_A: D4.2 (A), U3.32 (P0.02_AIN0)
NEO_LED: J1.1, TP10.1, U3.33 (P0.28_AIN4)
unnamed: ANT1.1 (FP), L2.2
unnamed: BT1.1 (+), R3.1
unnamed: BT1.2 (-), U2.2 (GND), U2.3 (GND), U2.7 (EP)
unnamed: C5.1, L1.2, L2.1
unnamed: D1.1 (K), R1.1
unnamed: D2.1 (I/O1), J3.A7 (D-), J3.B7 (D-)
unnamed: D2.3 (I/O2), J3.A6 (D+), J3.B6 (D+)
unnamed: D4.1 (K), R12.2
unnamed: J2.1, R9.1, TP11.1
unnamed: J3.A5 (CC1), R10.2
unnamed: J3.B5 (CC2), R11.2
unnamed: R4.1, U1.5 (PROG)
unnamed: R1.2, U1.1 (STAT)
unnamed: C8.1, L1.1, U3.24 (ANT)
unnamed: C2.2, U3.1 (DEC1)
unnamed: C11.1, U3.27 (DEC3)
unnamed: C9.2, U3.11 (DECUSB)
unnamed: C16.2, U3.2 (P0.00_XL1), Y2.2
unnamed: C15.2, U3.3 (P0.01_XL2), Y2.1
unnamed: R5.2, U3.16 (P0.18_nRESET)
unnamed: R6.1, U3.17 (P0.20)
unnamed: R7.1, U3.20 (SWDCLK)
unnamed: R8.2, U3.19 (SWDIO)
unnamed: C3.2, U3.28 (XC1), Y1.1
unnamed: C4.2, U3.29 (XC2), Y1.4
Pair: C14.2, R2.1, SW2.1, U3.35 (P0.30_AIN6)
SWDCLK_L: J3.A3 (TX1-), J3.B3 (TX2-), R8.1
SWDIO_L: J3.A2 (TX1+), J3.B2 (TX2+), R7.2
SWO_L: J3.A11 (RX2+), J3.B11 (RX1+), R6.2

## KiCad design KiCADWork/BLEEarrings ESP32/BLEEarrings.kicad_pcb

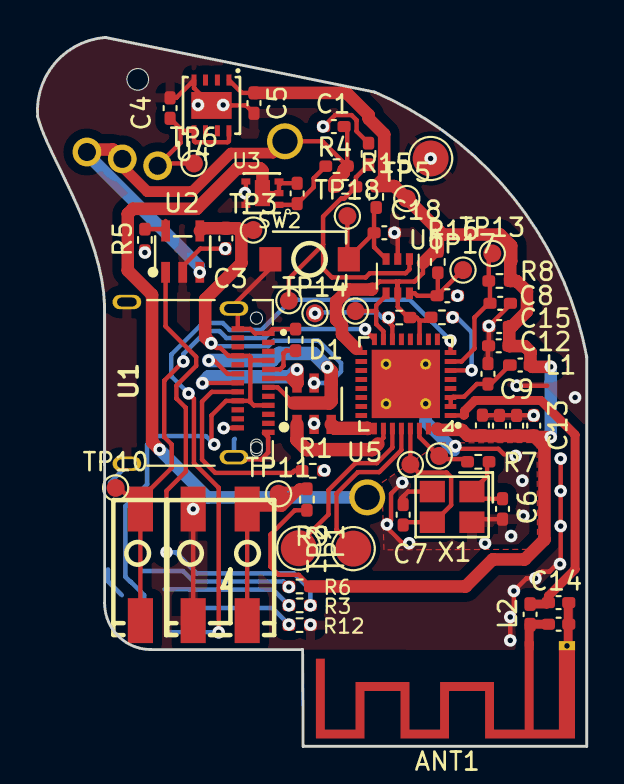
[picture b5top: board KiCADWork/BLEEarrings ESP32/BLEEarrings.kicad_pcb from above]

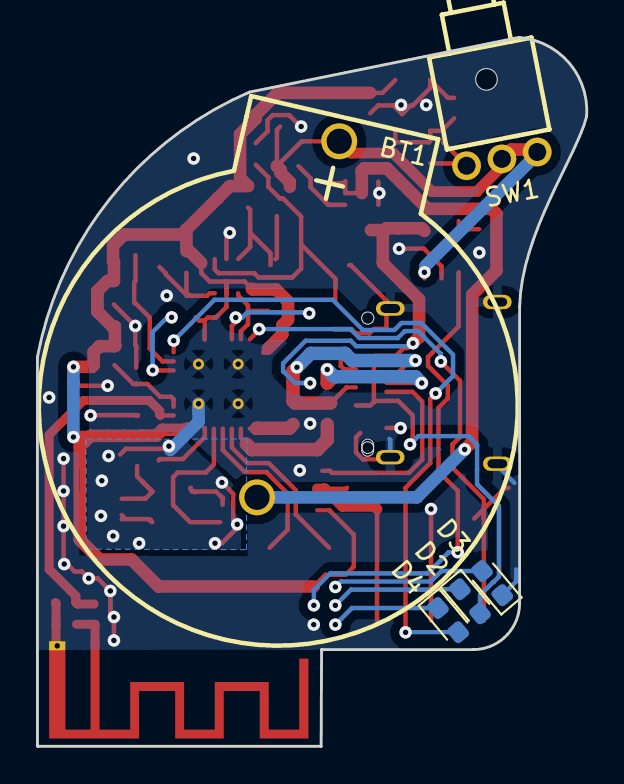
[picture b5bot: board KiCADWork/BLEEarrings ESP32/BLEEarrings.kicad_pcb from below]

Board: 2 copper layers, 30.5 x 39.4 mm, 70 parts (5 on the bottom side), 36 nets.

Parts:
ANT1: Texas_SWRA117D_2.4GHz_Right
BT1: Battery; BAT-TH_BS-24-A1AJ013
C1, C3, C15, C16: 10u; C_0402_1005Metric_Pad0.74x0.62mm_HandSolder
C2, C8, C9, C10, C11, C12, C13, C18: 100n; C_0402_1005Metric_Pad0.74x0.62mm_HandSolder
C4, C5, C19: 4.7u; C_0402_1005Metric_Pad0.74x0.62mm_HandSolder
C6, C7: 20pF; C_0402_1005Metric_Pad0.74x0.62mm_HandSolder
C14, C17: 3p3; C_0402_1005Metric_Pad0.74x0.62mm_HandSolder
D1: USBLC6-2SC6_C2687116; SOT-23-6_L2.9-W1.6-P0.95-LS2.8-BL
D2: WHITE LED; LED_0603_1608Metric_Pad1.05x0.95mm_HandSolder
D3: RED LED; LED_0603_1608Metric_Pad1.05x0.95mm_HandSolder
D4: BLUE LED; LED_0603_1608Metric_Pad1.05x0.95mm_HandSolder
J1: Screw_Terminal_01x01; CONN-SMD_custom1
J2: Screw_Terminal_01x02; CONN-SMD_2059-302
L1, L2: 2n2; L_0402_1005Metric_Pad0.77x0.64mm_HandSolder
R1, R2, R8, R10, R11, R13, R14, R15, R16: 5k1; R_0402_1005Metric_Pad0.72x0.64mm_HandSolder
R3, R5, R6, R12: 2k; R_0402_1005Metric_Pad0.72x0.64mm_HandSolder
R4: 100; R_0402_1005Metric_Pad0.72x0.64mm_HandSolder
R7: 22R; R_0402_1005Metric_Pad0.72x0.64mm_HandSolder
R9: 470; R_0402_1005Metric_Pad0.72x0.64mm_HandSolder
SW1: TK-6580B-1; SW-TH_TK-6580B-1
SW2: RESET SWITCH; SW-SMD_L3.9-W3.0-P4.45
TP1, TP2, TP16: TestPoint; TestPoint_Pad_D2.0mm
TP3, TP5, TP6, TP7, TP8, TP9, TP10, TP11, TP12, TP13, TP14, TP17, TP18: TestPoint; TestPoint_Pad_D1.0mm
U1: GT-USB-7010ASV; AMPHENOL_12401832E402A
U2: MCP73831T-2ACI/OT; SOT-23-5_L3.0-W1.7-P0.95-LS2.8-BL
U3: XB6096I2SV; WDFN-6_L2.0-W2.0-P0.65-BL-EP
U4: AP7361C-33FGE-7; DFN-8_L3.0-W3.0-P0.65-BL-EP
U5: ESP32-C3FH4; QFN-32_L5.0-W5.0-P0.50-TL-EP3.7
U6: TS5A3159ADCKR; SOT-363_SC-70-6
X1: 5YMA40000151SF40Q1; CRYSTAL-SMD_4P-L3.2-W2.5-BL

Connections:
+3V3: C5.1, C10.1, C11.1, C12.1, C13.1, C15.1, C16.1, L1.2, R6.1, R8.1, R9.2, R10.2, R11.2, R15.2, R16.2, TP5.1, U4.1 (OUT), U5.11 (VDD3P3_RTC), U5.17 (VDD3P3_CPU), U5.31 (VDDA), U5.32 (VDDA), U6.5 (V+)
+BATT: BT1.1 (+), C1.1, R4.2, R13.2, SW1.1, SW1.2, U2.3 (VBAT)
/D1+: D1.6 (I/O1), U1.A6 (DP1), U1.B6 (DP2)
/D1-: D1.4 (I/O2), U1.A7 (DN1), U1.B7 (DN2)
/D+: D1.1 (I/O1), U5.26 (GPIO19)
/D-: D1.3 (I/O2), U5.25 (GPIO18)
/Power/BATGND: BT1.2 (-), C2.2, U3.2 (GND), U3.3 (GND), U3.7 (EP)
/Power/VBUS: C3.1, D1.5 (VBUS), D2.2 (A), TP3.1, U1.A4B9 (VBUS), U1.B4A9 (VBUS), U2.4 (VDD)
BatRef: R13.1, R14.2, TP9.1, U6.1
GND: ANT1.2 (GND), C1.2, C3.2, C4.2, C5.2, C6.2, C7.2, C8.2, C9.2, C10.2, C11.2, C12.2, C13.2, C14.2, C15.2, C16.2, C17.2, C18.2, C19.2, D1.2 (GND), D3.1 (K), J2.1, R1.2, R2.2, R5.2, R12.1, R14.1, SW2.2 (D), TP16.1, U1.1 (SHELL), U1.2 (SHELL), U1.3 (SHELL), U1.4 (SHELL), U1.A1B12 (GND), U1.B1A12 (GND), U2.2 (VSS), U3.4 (VM), U3.5 (VM), U3.6 (VM), U4.4 (GND), U4.9 (EXP), U5.33 (GND), U5.A (THERMRELIEF), U6.2 (GND), X1.2 (GND), X1.4 (GND)
LED_A: D4.2 (A), U5.8 (GPIO3)
NEO_LED: J1.1, TP10.1, U5.16 (GPIO10)
unnamed: ANT1.1 (FP), C17.1, L2.2
unnamed: C6.1, R7.2, X1.1
unnamed: C9.1, L1.1, U5.2 (VDD3P3), U5.3 (VDD3P3)
unnamed: C19.1, R16.1, TP17.1, U6.6
unnamed: D2.1 (K), R3.1
unnamed: D3.2 (A), R6.2
unnamed: D4.1 (K), R12.2
unnamed: J2.2, R9.1, TP11.1
unnamed: C18.1, R15.1, SW2.1 (C), TP18.1, U6.3
unnamed: R2.1, U1.A5 (CC1)
unnamed: R1.1, U1.B5 (CC2)
unnamed: R5.1, U2.5 (PROG)
unnamed: R3.2, U2.1 (STAT)
unnamed: C2.1, R4.1, U3.1 (VDD)
unnamed: C4.1, SW1.3, TP6.1, U4.5 (EN), U4.8 (IN)
unnamed: C8.1, R8.2, TP13.1, U5.7 (CHIP_EN)
unnamed: R11.1, U5.6 (GPIO2)
unnamed: R10.1, TP14.1, U5.14 (GPIO8)
unnamed: C14.1, L2.1, U5.1 (LNA_IN)
unnamed: TP1.1, U5.27 (U0RXD)
unnamed: TP2.1, U5.28 (U0TXD)
unnamed: C7.1, TP8.1, U5.29 (XTAL_N), X1.3
unnamed: R7.1, TP7.1, U5.30 (XTAL_P)
RESET: TP12.1, U5.15 (GPIO9), U6.4

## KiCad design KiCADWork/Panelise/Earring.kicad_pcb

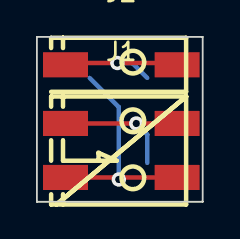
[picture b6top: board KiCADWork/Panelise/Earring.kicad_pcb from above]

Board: 2 copper layers, 9.2 x 9.2 mm, 3 parts (1 on the bottom side), 3 nets.

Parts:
D1: 2758; SOL320P540X170-4N
J1: Screw_Terminal_01x02; CONN-SMD_2059-302
J2: Screw_Terminal_01x01; CONN-SMD_custom1

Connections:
unnamed: D1.4 (DIN), J2.1
unnamed: D1.1 (VDD), J1.1
unnamed: D1.3 (VSS), J1.2

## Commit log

2022-12-08 Neopixel Blink
    Neopixel now blinks three times with set colour
2022-12-08 Toast To Success
    Button Added to App
2023-09-26 Schematic Started
2023-10-02 More KiCAD Work
    More KiCAD work complete
2023-10-30 First Draft Schematic Done
    - Symbols and footprints checked
    - Dom added to repo
    - Centralised footprints created
2023-11-23 Improved Antenna Layout
    - Initial layout complete
    - TO DO:
    - Test points
    - Curved Tracks
    - Silkscreen
    - Check antenna
2023-12-06 Large Update
2023-12-07 Small Bits
2023-12-08 New Chip NRF52833
    large changes
2023-12-12 Dock Updates
2024-01-08 Routing Started on Earrings Again
    - Only small routing changes made
2024-02-22 Ignoring Backups
    More Dock progress
    All local backups removed
2024-02-22 Small Updates
2024-02-22 Beautiful Skilkscreen Added
    Dock schematic intial draft complete
2024-02-22 Dock Updates
    Starting to layout the dock
    Dom still to check
2024-02-23 Initial Dock DRC Complete
2024-03-01 Starting the Panel
2024-03-27 Started mirror earrings and case
2024-04-28 Completing the combined layout
2024-04-28 Schem rev 1 pt1
2024-12-20 V1 BUILD
